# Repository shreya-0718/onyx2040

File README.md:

# Onyx2040
This is a devboard powered by the RP2040 chip! It features 40 pins broken out (20 per side) for easy prototyping and a plus‑sign of 5 RGB LEDs to animate whatever your heart desires.

I built this project as a way to learn full PCB design, from schematics to routing to firmware. It’s also a great way for others to prototype their own ideas, with colorful lighting built in to make experimentation more fun and expressive.

## How to Use It?
1. **Power the board** with USB-C
2. To use MicroPython, hold the button (the board will appear as a USB drive named RPI-RP2) and **flash the MicroPython UF2 firmware** with the [MicroPython RP2040 Documentation](https://www.raspberrypi.com/documentation/microcontrollers/micropython.html).
3. Once MicroPython is installed, **copy your Python files** to the board.
4. Then, **experiment!** Use the 40 broken‑out pins (GPIO, power, and ground) to connect sensors, modules, or breadboards. Check out the firmware in the /firmware folder in this repository for an example of how to control the on-board LEDs. Enjoy!

## Images
Here is the **schematic**:

And here is the **finished PCB** in the editor:

This is what the **final devboard** will look like:

## Bill of Materials (BOM)

| Item            | Description                  | Qty | Product Link | Price w/ Tax ($) | Running Total |
|-----------------|------------------------------|-----|--------------|------------------|---------------|
| Capacitor       | 1µF                          | 2   | https://jlcpcb.com/partdetail/53938-CL05A105KA5NQNC/C52923 | $0.03 | $0.03 |
| Capacitor       | 0.1µF                        | 11  | https://jlcpcb.com/partdetail/1877-CL05B104KO5NNNC/C1525   | $0.07 | $0.10 |
| Capacitor       | 10µF                         | 2   | https://jlcpcb.com/partdetail/2043-CL10A106MQ8NNNC/C1691   | $0.09 | $0.19 |
| Capacitor       | 33pF                         | 2   | https://jlcpcb.com/partdetail/1914-0402CG330J500NT/C1562   | $0.01 | $0.20 |
| Resistor        | 5.1kΩ                        | 2   | https://jlcpcb.com/partdetail/26648-0402WGF5101TCE/C25905  | $0.01 | $1.05 |
| Resistor        | 27Ω                          | 2   | https://jlcpcb.com/partdetail/25843-0402WGF270JTCE/C25100  | $0.01 | $1.06 |
| Resistor        | 330Ω                         | 1   | https://jlcpcb.com/partdetail/VikingTech-ARG02FTC3300/C284512 | $0.13 | $1.19 |
| Resistor        | 1kΩ                          | 2   | https://jlcpcb.com/partdetail/12256-0402WGF1001TCE/C11702  | $0.01 | $1.19 |
| Resistor        | 10kΩ                         | 1   | https://jlcpcb.com/partdetail/26487-0402WGF1002TCE/C25744  | $0.00 | $1.20 |
| SW Push         | Button                       | 1   | https://www.lcsc.com/product-detail/C720477.html           | $0.42 | $11.33 |
| WS2812B-2020    | RGB SMD LEDs                 | 5   | https://www.lcsc.com/product-detail/C965555.html           | —     | $1.04 |
| RP2040          | Microcontroller              | 1   | https://jlcpcb.com/partdetail/RaspberryPi-RP2040/C2040     | $4.58 | $5.78 |
| USB Receptacle  | USB-C (USB2.0, 14P)          | 1   | https://jlcpcb.com/partdetail/Korean_HropartsElec-TYPE_C_31_M12/C165948 | $0.85 | $1.04 |
| MCP1700x-330xxTT| Voltage Regulator            | 1   | https://jlcpcb.com/partdetail/MicrochipTech-MCP1700T_3302ETT/C39051 | $1.97 | $7.75 |
| W25Q16JVSS      | Firmware storage             | 1   | https://jlcpcb.com/partdetail/WinbondElec-W25Q16JVSSIQ/C82317 | $2.67 | $10.42 |
| Crystal         | Quartz resonator, 12 MHz     | 1   | https://jlcpcb.com/partdetail/YXC_CrystalOscillators-X322512MSB4SI/C9002 | $0.32 | $10.74 |
| Conn_01x03      | 1x03 Pin Header              | 1   | https://www.lcsc.com/product-detail/C42431804.html         | $0.00 | $10.74 |
| Conn_01x20      | 1x20 Pin Headers             | 2   | https://www.lcsc.com/product-detail/C42431804.html         | $0.17 | $10.91 |
| Onyx2040 PCBA   | Board assembly               | 1   | https://cart.jlcpcb.com/                                    | $43.94 | $54.85 |

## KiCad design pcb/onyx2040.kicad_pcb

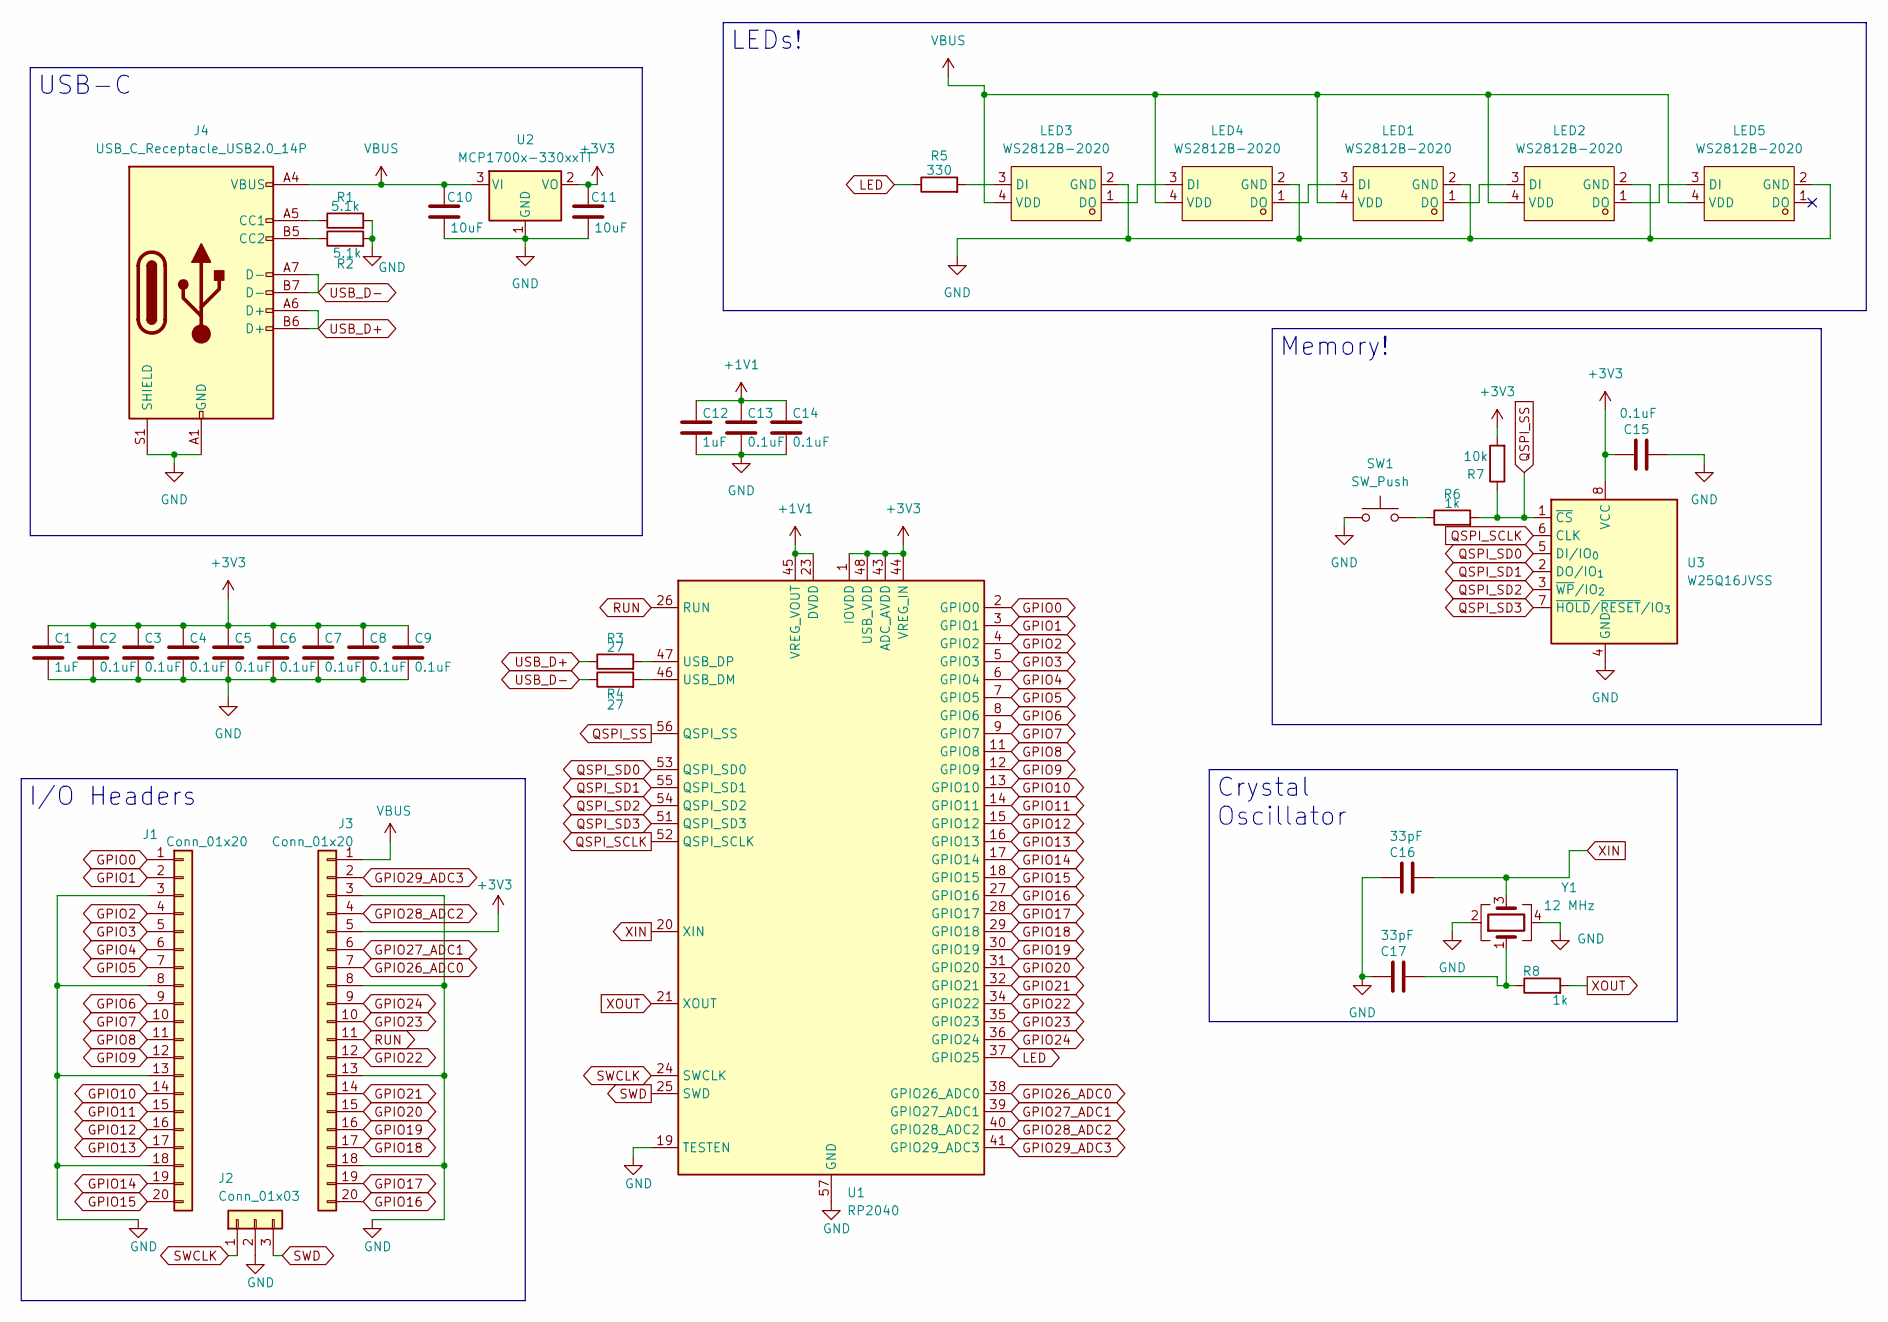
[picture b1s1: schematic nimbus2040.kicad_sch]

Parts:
C1, C12: 1uF; C_0402_1005Metric
C2, C3, C4, C5, C6, C7, C8, C9, C13, C14, C15: 0.1uF; C_0402_1005Metric
C10, C11: 10uF; C_0603_1608Metric
C16, C17: 33pF; C_0402_1005Metric
J1, J3: Conn_01x20; PinHeader_1x20_P2.54mm_Vertical
J2: Conn_01x03; PinHeader_1x03_P2.54mm_Vertical
J4: USB_C_Receptacle_USB2.0_14P; USB_C_Receptacle_HRO_TYPE-C-31-M-12
LED1, LED2, LED3, LED4, LED5: WS2812B-2020; LED-SMD_4P-L2.0-W2.0-TL_WS2812B-2020; LCSC Part C965555
R1, R2: 5.1k; R_0402_1005Metric
R3, R4: 27; R_0402_1005Metric
R5: 330; R_0402_1005Metric
R6, R8: 1k; R_0402_1005Metric
R7: 10k; R_0402_1005Metric
SW1: SW_Push; SW_Push_SPST_NO_Alps_SKRK
U1: RP2040; QFN-56-1EP_7x7mm_P0.4mm_EP3.2x3.2mm
U2: MCP1700x-330xxTT; SOT-23
U3: W25Q16JVSS; SOIC-8_5.3x5.3mm_P1.27mm
Y1: 12 MHz; Crystal_SMD_3225-4Pin_3.2x2.5mm

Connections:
+1V1: C12.1, C13.1, C14.1, U1.23 (DVDD), U1.45 (VREG_VOUT), U1.50 (DVDD)
+3V3: C1.1, C2.1, C3.1, C4.1, C5.1, C6.1, C7.1, C8.1, C9.1, C11.1, C15.1, J3.5, R7.2, U1.1 (IOVDD), U1.10 (IOVDD), U1.22 (IOVDD), U1.33 (IOVDD), U1.42 (IOVDD), U1.43 (ADC_AVDD), U1.44 (VREG_IN), U1.48 (USB_VDD), U1.49 (IOVDD), U2.2 (VO), U3.8 (VCC)
GND: C1.2, C2.2, C3.2, C4.2, C5.2, C6.2, C7.2, C8.2, C9.2, C10.2, C11.2, C12.2, C13.2, C14.2, C15.2, C16.1, C17.1, J1.3, J1.8, J1.13, J1.18, J2.2, J3.3, J3.8, J3.13, J3.18, J4.A1 (GND), J4.A12 (GND), J4.B1 (GND), J4.B12 (GND), J4.S1 (SHIELD), LED1.2 (GND), LED2.2 (GND), LED3.2 (GND), LED4.2 (GND), LED5.2 (GND), R1.2, R2.2, SW1.1, U1.19 (TESTEN), U1.57 (GND), U2.1 (GND), U3.4 (GND), Y1.2, Y1.4
GPIO0: J1.1, U1.2 (GPIO0)
GPIO1: J1.2, U1.3 (GPIO1)
GPIO2: J1.4, U1.4 (GPIO2)
GPIO3: J1.5, U1.5 (GPIO3)
GPIO4: J1.6, U1.6 (GPIO4)
GPIO5: J1.7, U1.7 (GPIO5)
GPIO6: J1.9, U1.8 (GPIO6)
GPIO7: J1.10, U1.9 (GPIO7)
GPIO8: J1.11, U1.11 (GPIO8)
GPIO9: J1.12, U1.12 (GPIO9)
GPIO10: J1.14, U1.13 (GPIO10)
GPIO11: J1.15, U1.14 (GPIO11)
GPIO12: J1.16, U1.15 (GPIO12)
GPIO13: J1.17, U1.16 (GPIO13)
GPIO14: J1.19, U1.17 (GPIO14)
GPIO15: J1.20, U1.18 (GPIO15)
GPIO16: J3.20, U1.27 (GPIO16)
GPIO17: J3.19, U1.28 (GPIO17)
GPIO18: J3.17, U1.29 (GPIO18)
GPIO19: J3.16, U1.30 (GPIO19)
GPIO20: J3.15, U1.31 (GPIO20)
GPIO21: J3.14, U1.32 (GPIO21)
GPIO22: J3.12, U1.34 (GPIO22)
GPIO23: J3.10, U1.35 (GPIO23)
GPIO24: J3.9, U1.36 (GPIO24)
GPIO26_ADC0: J3.7, U1.38 (GPIO26_ADC0)
GPIO27_ADC1: J3.6, U1.39 (GPIO27_ADC1)
GPIO28_ADC2: J3.4, U1.40 (GPIO28_ADC2)
GPIO29_ADC3: J3.2, U1.41 (GPIO29_ADC3)
LED: R5.1, U1.37 (GPIO25)
unnamed: C17.2, R8.1, Y1.1
unnamed: J4.A5 (CC1), R1.1
unnamed: J4.B5 (CC2), R2.1
unnamed: LED1.3 (DI), LED4.1 (DO)
unnamed: LED1.1 (DO), LED2.3 (DI)
unnamed: LED2.1 (DO), LED5.3 (DI)
unnamed: LED3.3 (DI), R5.2
unnamed: LED3.1 (DO), LED4.3 (DI)
unnamed: R6.1, SW1.2
unnamed: R4.2, U1.46 (USB_DM)
unnamed: R3.2, U1.47 (USB_DP)
QSPI_SCLK: U1.52 (QSPI_SCLK), U3.6 (CLK)
QSPI_SD0: U1.53 (QSPI_SD0), U3.5 (DI/IO_{0})
QSPI_SD1: U1.55 (QSPI_SD1), U3.2 (DO/IO_{1})
QSPI_SD2: U1.54 (QSPI_SD2), U3.3 (~WP/IO_{2})
QSPI_SD3: U1.51 (QSPI_SD3), U3.7 (~HOLD/~RESET/IO_{3})
QSPI_SS: R6.2, R7.1, U1.56 (QSPI_SS), U3.1 (~CS)
RUN: J3.11, U1.26 (RUN)
SWCLK: J2.1, U1.24 (SWCLK)
SWD: J2.3, U1.25 (SWD)
USB_D+: J4.A6 (D+), J4.B6 (D+), R3.1
USB_D-: J4.A7 (D-), J4.B7 (D-), R4.1
VBUS: C10.1, J3.1, J4.A4 (VBUS), J4.A9 (VBUS), J4.B4 (VBUS), J4.B9 (VBUS), LED1.4 (VDD), LED2.4 (VDD), LED3.4 (VDD), LED4.4 (VDD), LED5.4 (VDD), U2.3 (VI)
XIN: C16.2, U1.20 (XIN), Y1.3
XOUT: R8.2, U1.21 (XOUT)

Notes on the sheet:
Memory!
I/O Headers
Crystal Oscillator
LEDs!
USB-C

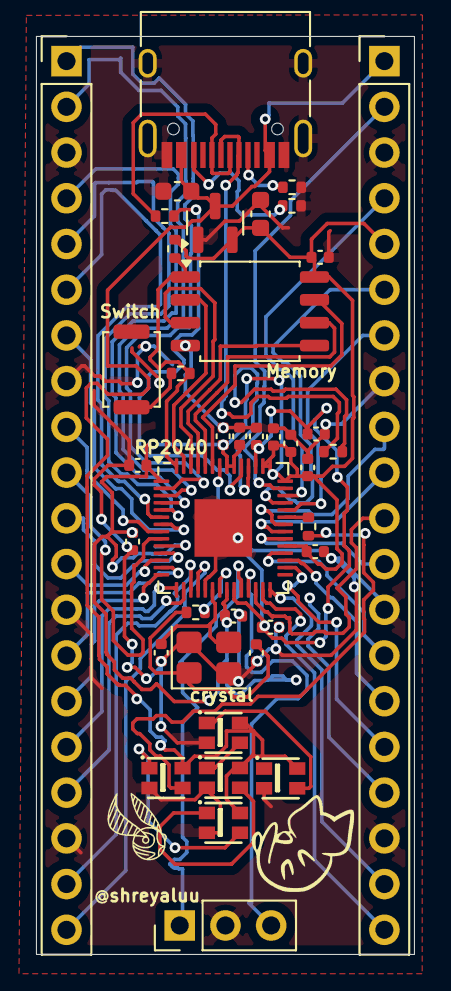
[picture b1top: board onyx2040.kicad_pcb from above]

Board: 2 copper layers, 21.0 x 51.0 mm, 39 parts (0 on the bottom side), 58 nets.

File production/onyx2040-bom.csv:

Id,Designator,Footprint,Quantity,Comment,Supplier and ref
1,"R1,R2",R_0402_1005Metric,2,5.1k,
2,"LED1,LED5,LED4,LED2,LED3",LED-SMD_4P-L2.0-W2.0-TL_WS2812B-2020,5,WS2812B-2020,
3,"R4,R3",R_0402_1005Metric,2,27,
4,"C6,C7,C9,C4,C15,C5,C13,C8,C14,C2,C3",C_0402_1005Metric,11,0.1uF,
5,"J3,J1",PinHeader_1x20_P2.54mm_Vertical,2,Conn_01x20,
6,U3,SOIC-8_5.3x5.3mm_P1.27mm,1,W25Q16JVSS,
7,R7,R_0402_1005Metric,1,10k,
8,"C16,C17",C_0402_1005Metric,2,33pF,
9,"C1,C12",C_0402_1005Metric,2,1uF,
10,R5,R_0402_1005Metric,1,330,
11,U1,QFN-56-1EP_7x7mm_P0.4mm_EP3.2x3.2mm,1,RP2040,
12,Y1,Crystal_SMD_3225-4Pin_3.2x2.5mm,1,12 MHz,
13,"R6,R8",R_0402_1005Metric,2,1k,
14,"C10,C11",C_0603_1608Metric,2,10uF,
15,U2,SOT-23,1,MCP1700x-330xxTT,
16,J4,USB_C_Receptacle_HRO_TYPE-C-31-M-12,1,USB_C_Receptacle_USB2.0_14P,
17,J2,PinHeader_1x03_P2.54mm_Vertical,1,Conn_01x03,
18,SW1,SW_Push_SPST_NO_Alps_SKRK,1,SW_Push,

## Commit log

2025-11-26 file organization
2025-11-26 publish to main
2025-11-26 added cad file
2025-11-26 added firmware code
2025-11-27 made BOM! and production files!
2025-11-27 Update README with how-to-use instructions
2025-11-27 cleaned up pcb files
2025-11-27 removed bom from gitignore
2025-11-27 update BOM
2025-11-28 changed color of pcb
